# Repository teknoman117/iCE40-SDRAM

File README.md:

# iCE40-SDRAM

An (unofficial) SDRAM module for the [Olimex iCE40HX8K-EVB](https://www.olimex.com/Products/FPGA/iCE40/iCE40HX8K-EVB/open-source-hardware)

### Notes

Untested as of 27 July 2022. Initial PCBs received but not assembled or tested yet.

### License

CC-BY-SA 4.0

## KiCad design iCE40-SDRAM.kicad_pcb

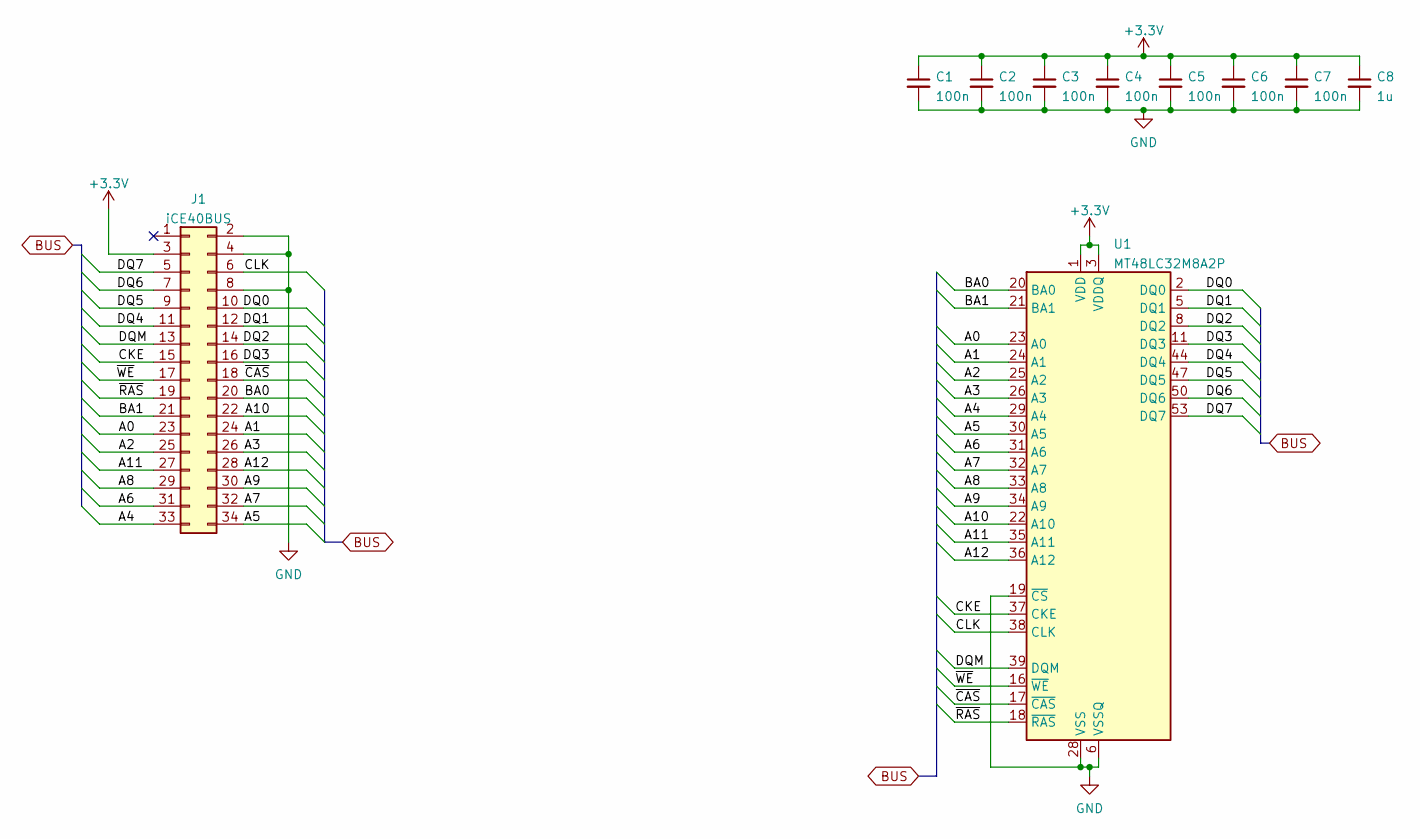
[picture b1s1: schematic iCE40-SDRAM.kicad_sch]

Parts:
C1, C2, C3, C4, C5, C6, C7: 100n; C_0603_1608Metric_Pad1.08x0.95mm_HandSolder
C8: 1u; C_0603_1608Metric_Pad1.08x0.95mm_HandSolder
J1: iCE40BUS; PinHeader_2x17_P2.54mm_Vertical
U1: MT48LC32M8A2P; TSOP-II-54_22.2x10.16mm_P0.8mm

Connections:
+3V3: C1.1, C2.1, C3.1, C4.1, C5.1, C6.1, C7.1, C8.1, J1.3, U1.1 (VDD), U1.3 (VDDQ), U1.9 (VDDQ), U1.14 (VDD), U1.27 (VDD), U1.43 (VDDQ), U1.49 (VDDQ)
/A0: J1.23, U1.23 (A0)
/A1: J1.24, U1.24 (A1)
/A2: J1.25, U1.25 (A2)
/A3: J1.26, U1.26 (A3)
/A4: J1.33, U1.29 (A4)
/A5: J1.34, U1.30 (A5)
/A6: J1.31, U1.31 (A6)
/A7: J1.32, U1.32 (A7)
/A8: J1.29, U1.33 (A8)
/A9: J1.30, U1.34 (A9)
/A10: J1.22, U1.22 (A10)
/A11: J1.27, U1.35 (A11)
/A12: J1.28, U1.36 (A12)
/BA0: J1.20, U1.20 (BA0)
/BA1: J1.21, U1.21 (BA1)
/CKE: J1.15, U1.37 (CKE)
/CLK: J1.6, U1.38 (CLK)
/DQ0: J1.10, U1.2 (DQ0)
/DQ1: J1.12, U1.5 (DQ1)
/DQ2: J1.14, U1.8 (DQ2)
/DQ3: J1.16, U1.11 (DQ3)
/DQ4: J1.11, U1.44 (DQ4)
/DQ5: J1.9, U1.47 (DQ5)
/DQ6: J1.7, U1.50 (DQ6)
/DQ7: J1.5, U1.53 (DQ7)
/DQM: J1.13, U1.39 (DQM)
/~CAS: J1.18, U1.17 (~CAS)
/~RAS: J1.19, U1.18 (~RAS)
/~WE: J1.17, U1.16 (~WE)
GND: C1.2, C2.2, C3.2, C4.2, C5.2, C6.2, C7.2, C8.2, J1.2, J1.4, J1.8, U1.6 (VSSQ), U1.12 (VSSQ), U1.19 (~CS), U1.28 (VSS), U1.41 (VSS), U1.46 (VSSQ), U1.52 (VSSQ), U1.54 (VSS)

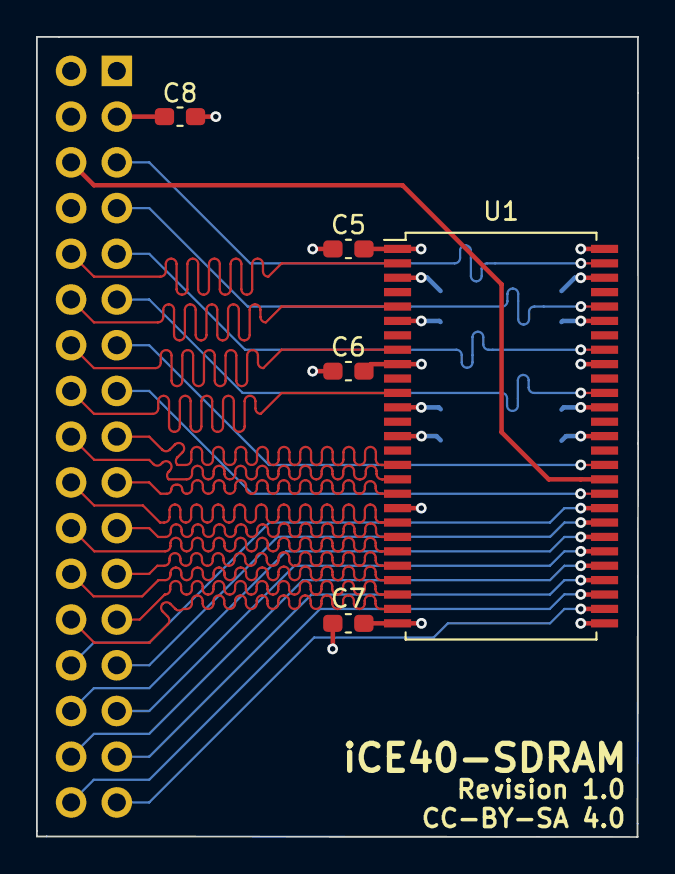
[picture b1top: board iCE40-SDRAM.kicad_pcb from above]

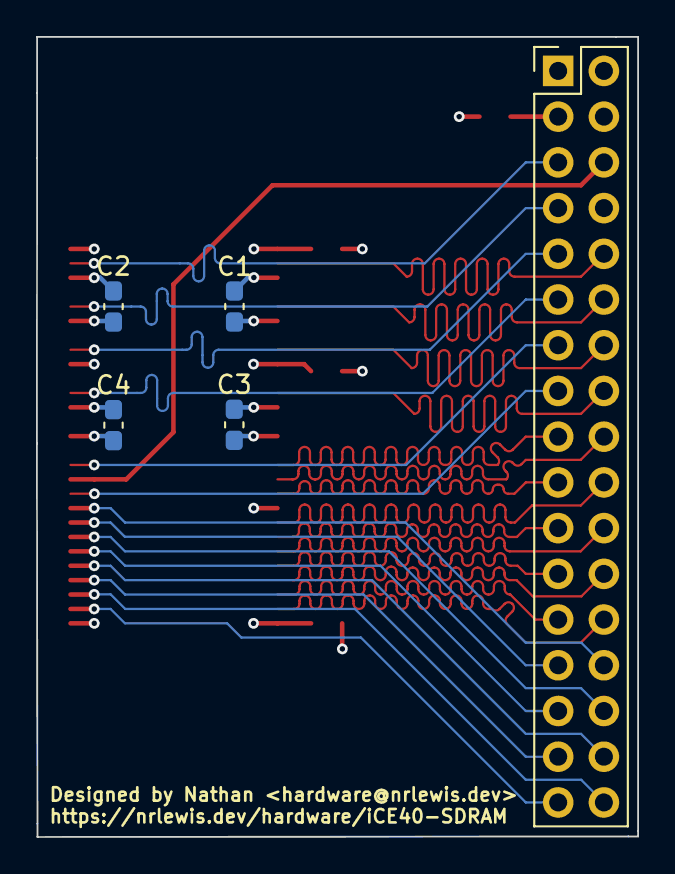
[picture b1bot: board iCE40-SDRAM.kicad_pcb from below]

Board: 4 copper layers, 33.4 x 44.5 mm, 10 parts (5 on the bottom side), 31 nets.

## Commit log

2022-07-28 change gerber output name
